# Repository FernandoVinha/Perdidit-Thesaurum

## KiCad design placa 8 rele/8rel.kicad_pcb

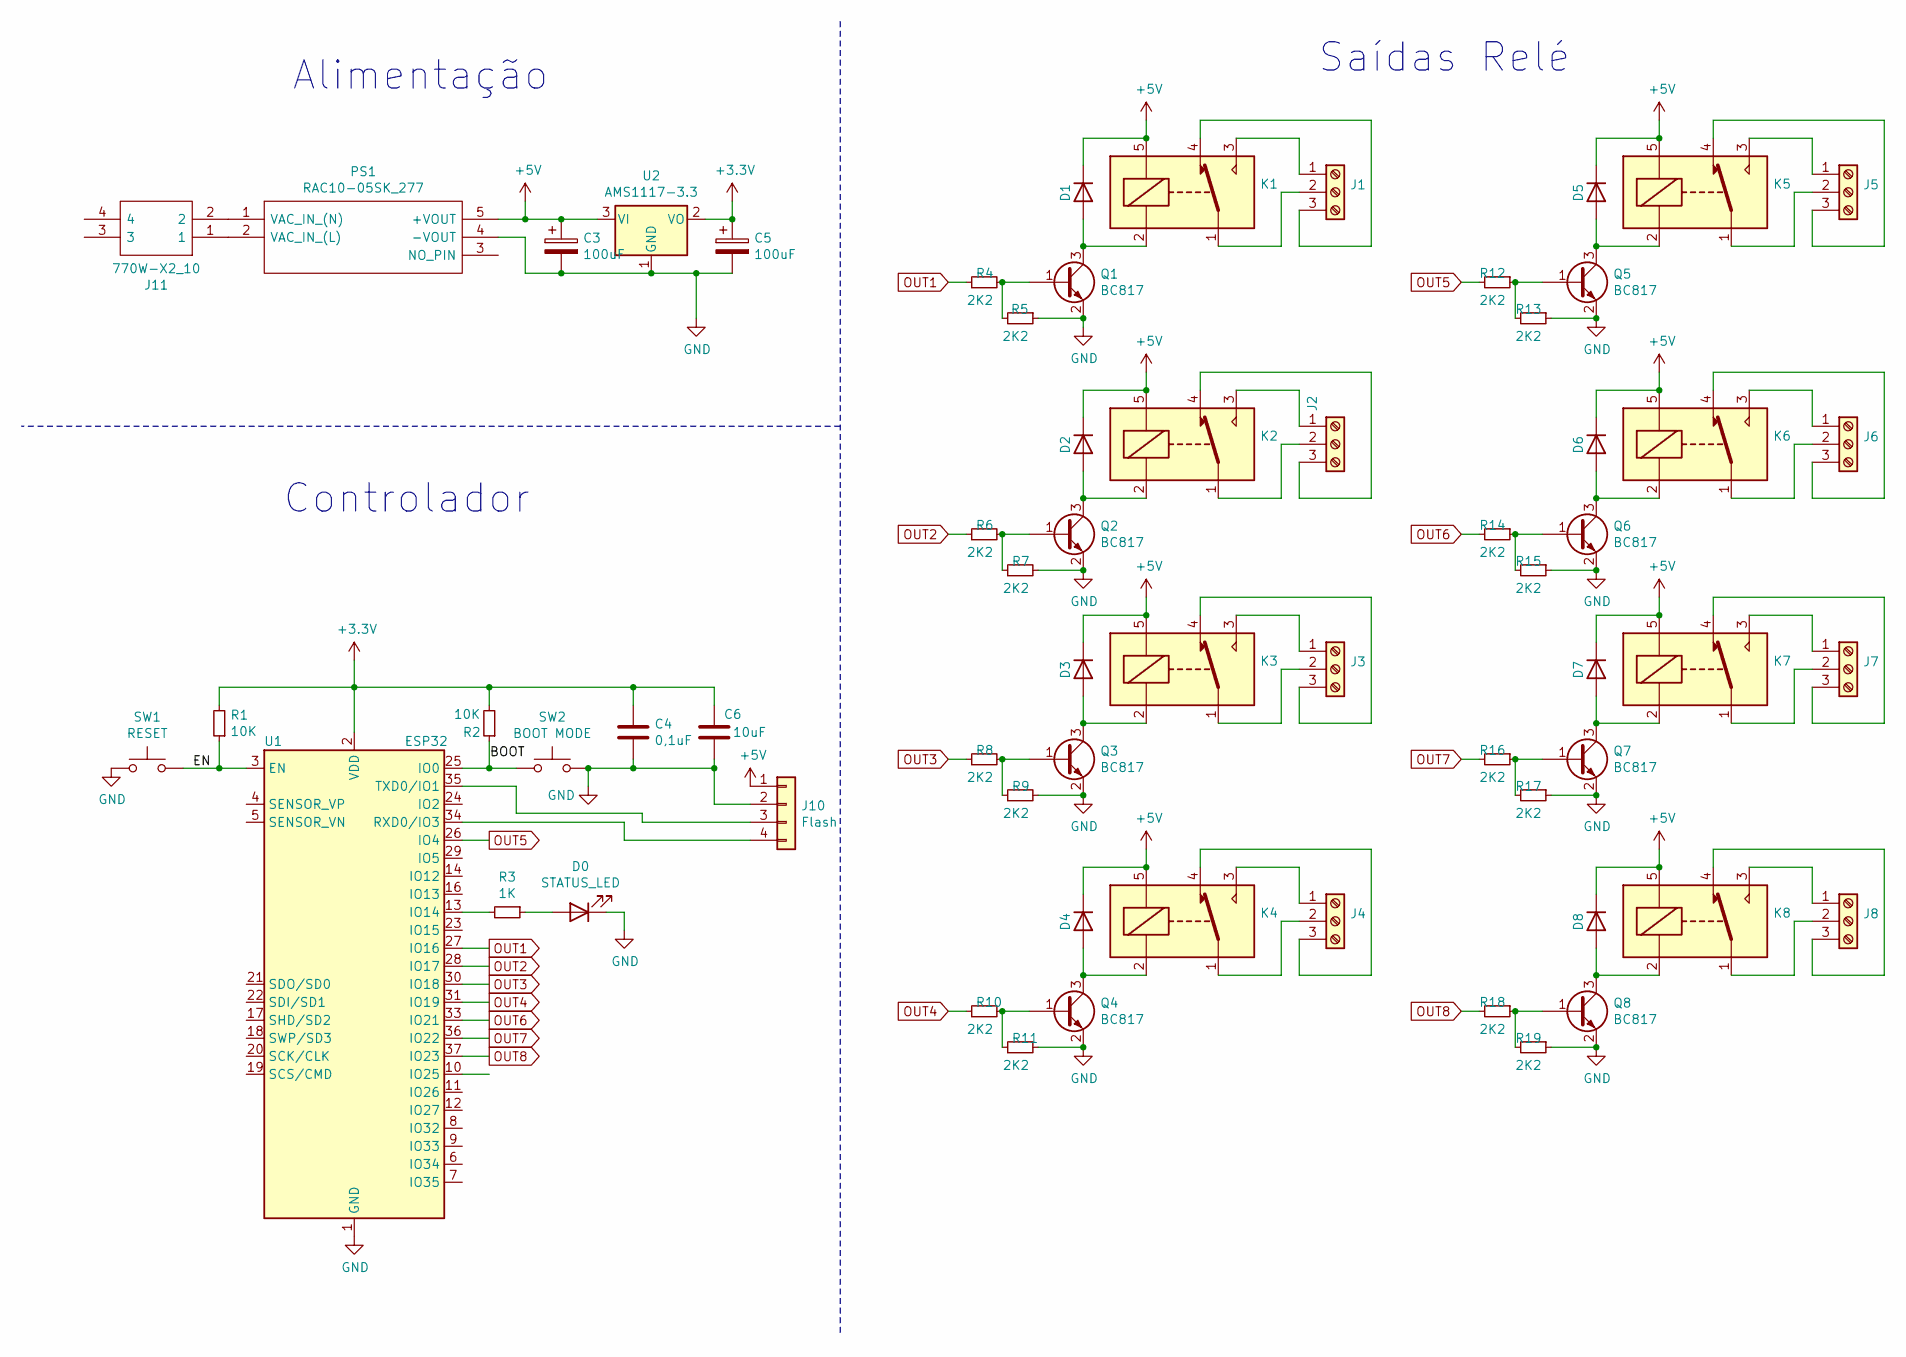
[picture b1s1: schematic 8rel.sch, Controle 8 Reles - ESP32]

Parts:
C3, C5: 100uF; CP_Radial_D5.0mm_P2.50mm
C4: 0,1uF; C_0805_2012Metric_Pad1.15x1.40mm_HandSolder
C6: 10uF; C_0805_2012Metric_Pad1.15x1.40mm_HandSolder
D0: STATUS_LED; LED_D3.0mm
D1, D2: DIODE; D_DO-41_SOD81_P10.16mm_Horizontal
D3, D4, D5, D6, D7, D8: DIODE
J1, J2, J3, J4, J5, J6, J7, J8: Screw_Terminal_01x03; PhoenixContact_MSTBA_2,5_3-G-5,08_1x03_P5.08mm_Horizontal
J10: Flash; PinHeader_1x04_P2.54mm_Vertical
J11: 770W-X2_10; 770WX210; Mouser Part Number 562-770W-X2/10
K1, K2, K3, K4, K5, K6, K7, K8: SANYOU_SRD_Form_C; Relay_SPDT_SANYOU_SRD_Series_Form_C
PS1: RAC10-05SK_277; RAC1005SK277; Manufacturer_Part_Number RAC10-05SK/277; Mouser Part Number 919-RAC10-05SK/277
Q1, Q2, Q3, Q4, Q5, Q6, Q7, Q8: BC817; SOT-23
R1, R2: 10K; R_0805_2012Metric_Pad1.15x1.40mm_HandSolder
R3: 1K; R_0805_2012Metric_Pad1.15x1.40mm_HandSolder
R4, R5, R6, R7, R8, R9, R10, R11, R12, R13, R14, R15, R16, R17, R18, R19: 2K2; R_0805_2012Metric_Pad1.15x1.40mm_HandSolder
SW1: RESET; SW_PUSH_6mm
SW2: BOOT MODE; SW_PUSH_6mm
U1: ESP32; ESP32-WROOM-32
U2: AMS1117-3.3; SOT-223-3_TabPin2

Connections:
+3V3: C4.1, C5.1, C6.1, R1.2, R2.2, U1.2 (VDD), U2.2 (VO)
+5V: C3.1, D1.2 (K), D2.2 (K), D3.2 (K), D4.2 (K), D5.2 (K), D6.2 (K), D7.2 (K), D8.2 (K), J10.1, K1.5, K2.5, K3.5, K4.5, K5.5, K6.5, K7.5, K8.5, PS1.5 (+VOUT), U2.3 (VI)
/BOOT: R2.1, SW2.1, U1.25 (IO0)
/EN: R1.1, SW1.2, U1.3 (EN)
GND: C3.2, C4.2, C5.2, C6.2, D0.1 (K), J10.2, PS1.4 (-VOUT), Q1.2 (E), Q2.2 (E), Q3.2 (E), Q4.2 (E), Q5.2 (E), Q6.2 (E), Q7.2 (E), Q8.2 (E), R5.1, R7.2, R9.2, R11.2, R13.1, R15.1, R17.1, R19.1, SW1.1, SW2.2, U1.1 (GND), U1.15 (GND), U1.38 (GND), U1.39 (GND), U2.1 (GND)
unnamed: D0.2 (A), R3.1
unnamed: D1.1 (A), K1.2, Q1.3 (C)
unnamed: D2.1 (A), K2.2, Q2.3 (C)
unnamed: D3.1 (A), K3.2, Q3.3 (C)
unnamed: D4.1 (A), K4.2, Q4.3 (C)
unnamed: D5.1 (A), K5.2, Q5.3 (C)
unnamed: D6.1 (A), K6.2, Q6.3 (C)
unnamed: D7.1 (A), K7.2, Q7.3 (C)
unnamed: D8.1 (A), K8.2, Q8.3 (C)
unnamed: J1.1, K1.3
unnamed: J1.2, K1.1
unnamed: J1.3, K1.4
unnamed: J2.1, K2.3
unnamed: J2.2, K2.1
unnamed: J2.3, K2.4
unnamed: J3.1, K3.3
unnamed: J3.2, K3.1
unnamed: J3.3, K3.4
unnamed: J4.1, K4.3
unnamed: J4.2, K4.1
unnamed: J4.3, K4.4
unnamed: J5.1, K5.3
unnamed: J5.2, K5.1
unnamed: J5.3, K5.4
unnamed: J6.1, K6.3
unnamed: J6.2, K6.1
unnamed: J6.3, K6.4
unnamed: J7.1, K7.3
unnamed: J7.2, K7.1
unnamed: J7.3, K7.4
unnamed: J8.1, K8.3
unnamed: J8.2, K8.1
unnamed: J8.3, K8.4
unnamed: J10.3, U1.35 (TXD0/IO1)
unnamed: J10.4, U1.34 (RXD0/IO3)
unnamed: J11.1, PS1.2 (VAC_IN_(L))
unnamed: J11.2, PS1.1 (VAC_IN_(N))
unnamed: Q1.1 (B), R4.2, R5.2
unnamed: Q2.1 (B), R6.2, R7.1
unnamed: Q3.1 (B), R8.2, R9.1
unnamed: Q4.1 (B), R10.2, R11.1
unnamed: Q5.1 (B), R12.1, R13.2
unnamed: Q6.1 (B), R14.1, R15.2
unnamed: Q7.1 (B), R16.1, R17.2
unnamed: Q8.1 (B), R18.1, R19.2
unnamed: R3.2, U1.13 (IO14)
OUT1: R4.1, U1.27 (IO16)
OUT2: R6.1, U1.28 (IO17)
OUT3: R8.1, U1.30 (IO18)
OUT4: R10.1, U1.31 (IO19)
OUT5: R12.2, U1.26 (IO4)
OUT6: R14.2, U1.33 (IO21)
OUT7: R16.2, U1.36 (IO22)
OUT8: R18.2, U1.37 (IO23)

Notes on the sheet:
Alimentação
Saídas Relé
Controlador

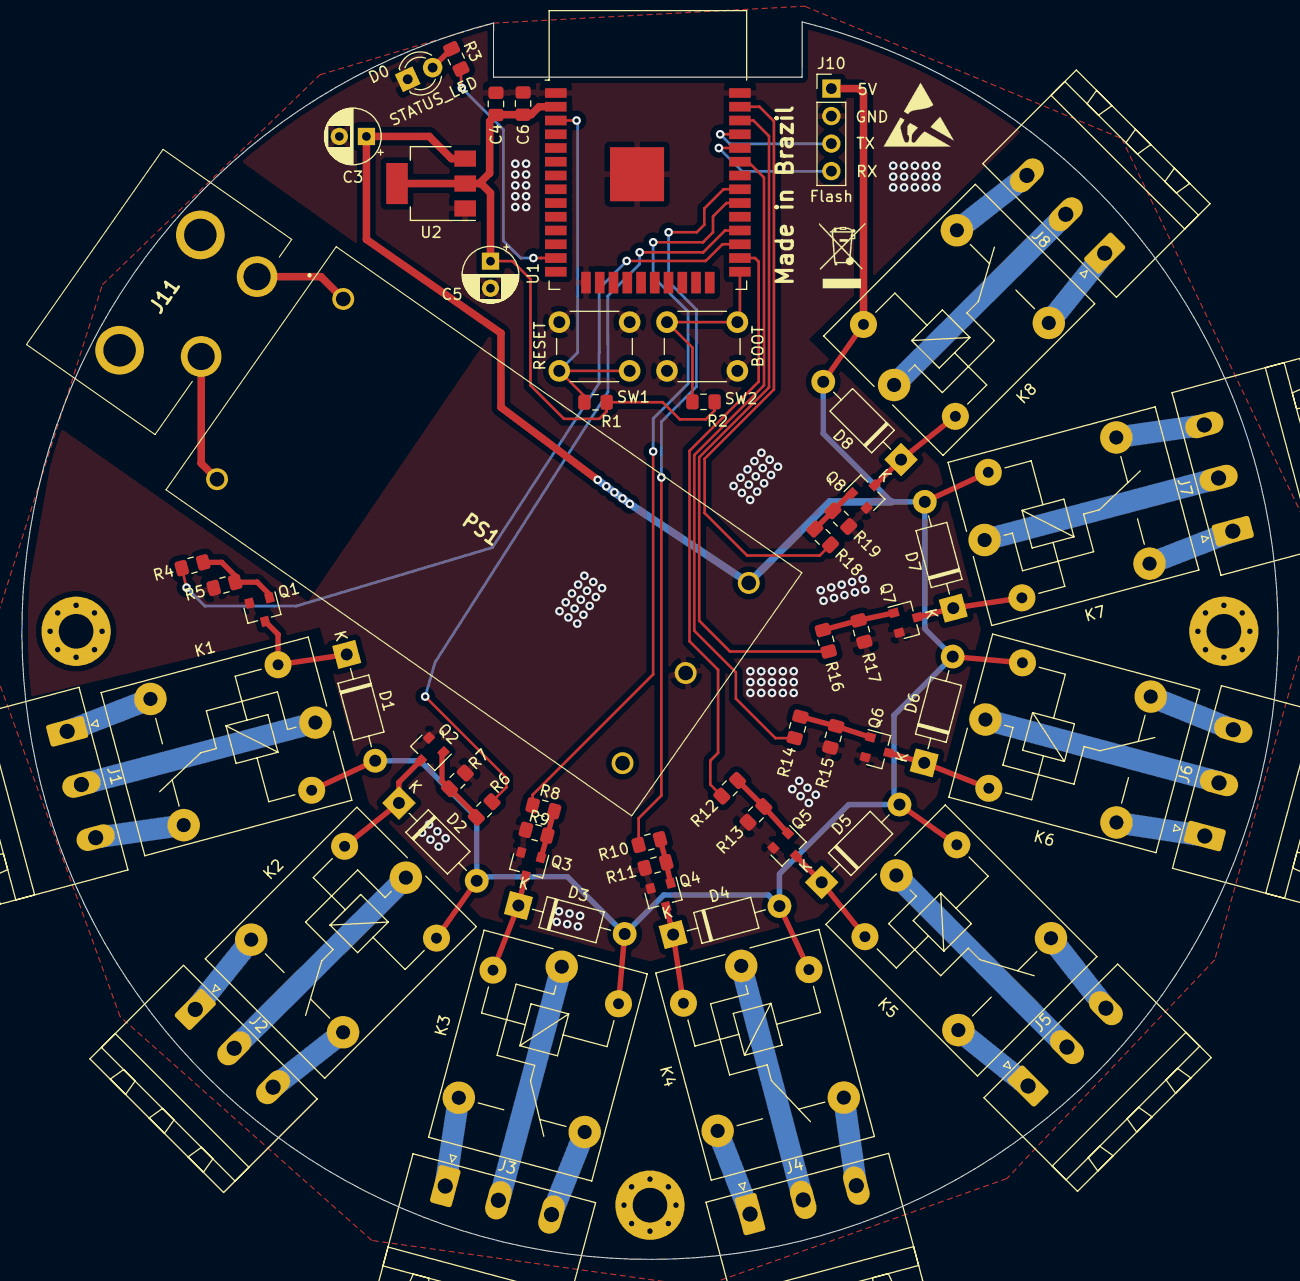
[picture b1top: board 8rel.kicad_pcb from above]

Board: 2 copper layers, 116.0 x 114.3 mm, 63 parts (0 on the bottom side), 59 nets.

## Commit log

2021-03-02 image+material
